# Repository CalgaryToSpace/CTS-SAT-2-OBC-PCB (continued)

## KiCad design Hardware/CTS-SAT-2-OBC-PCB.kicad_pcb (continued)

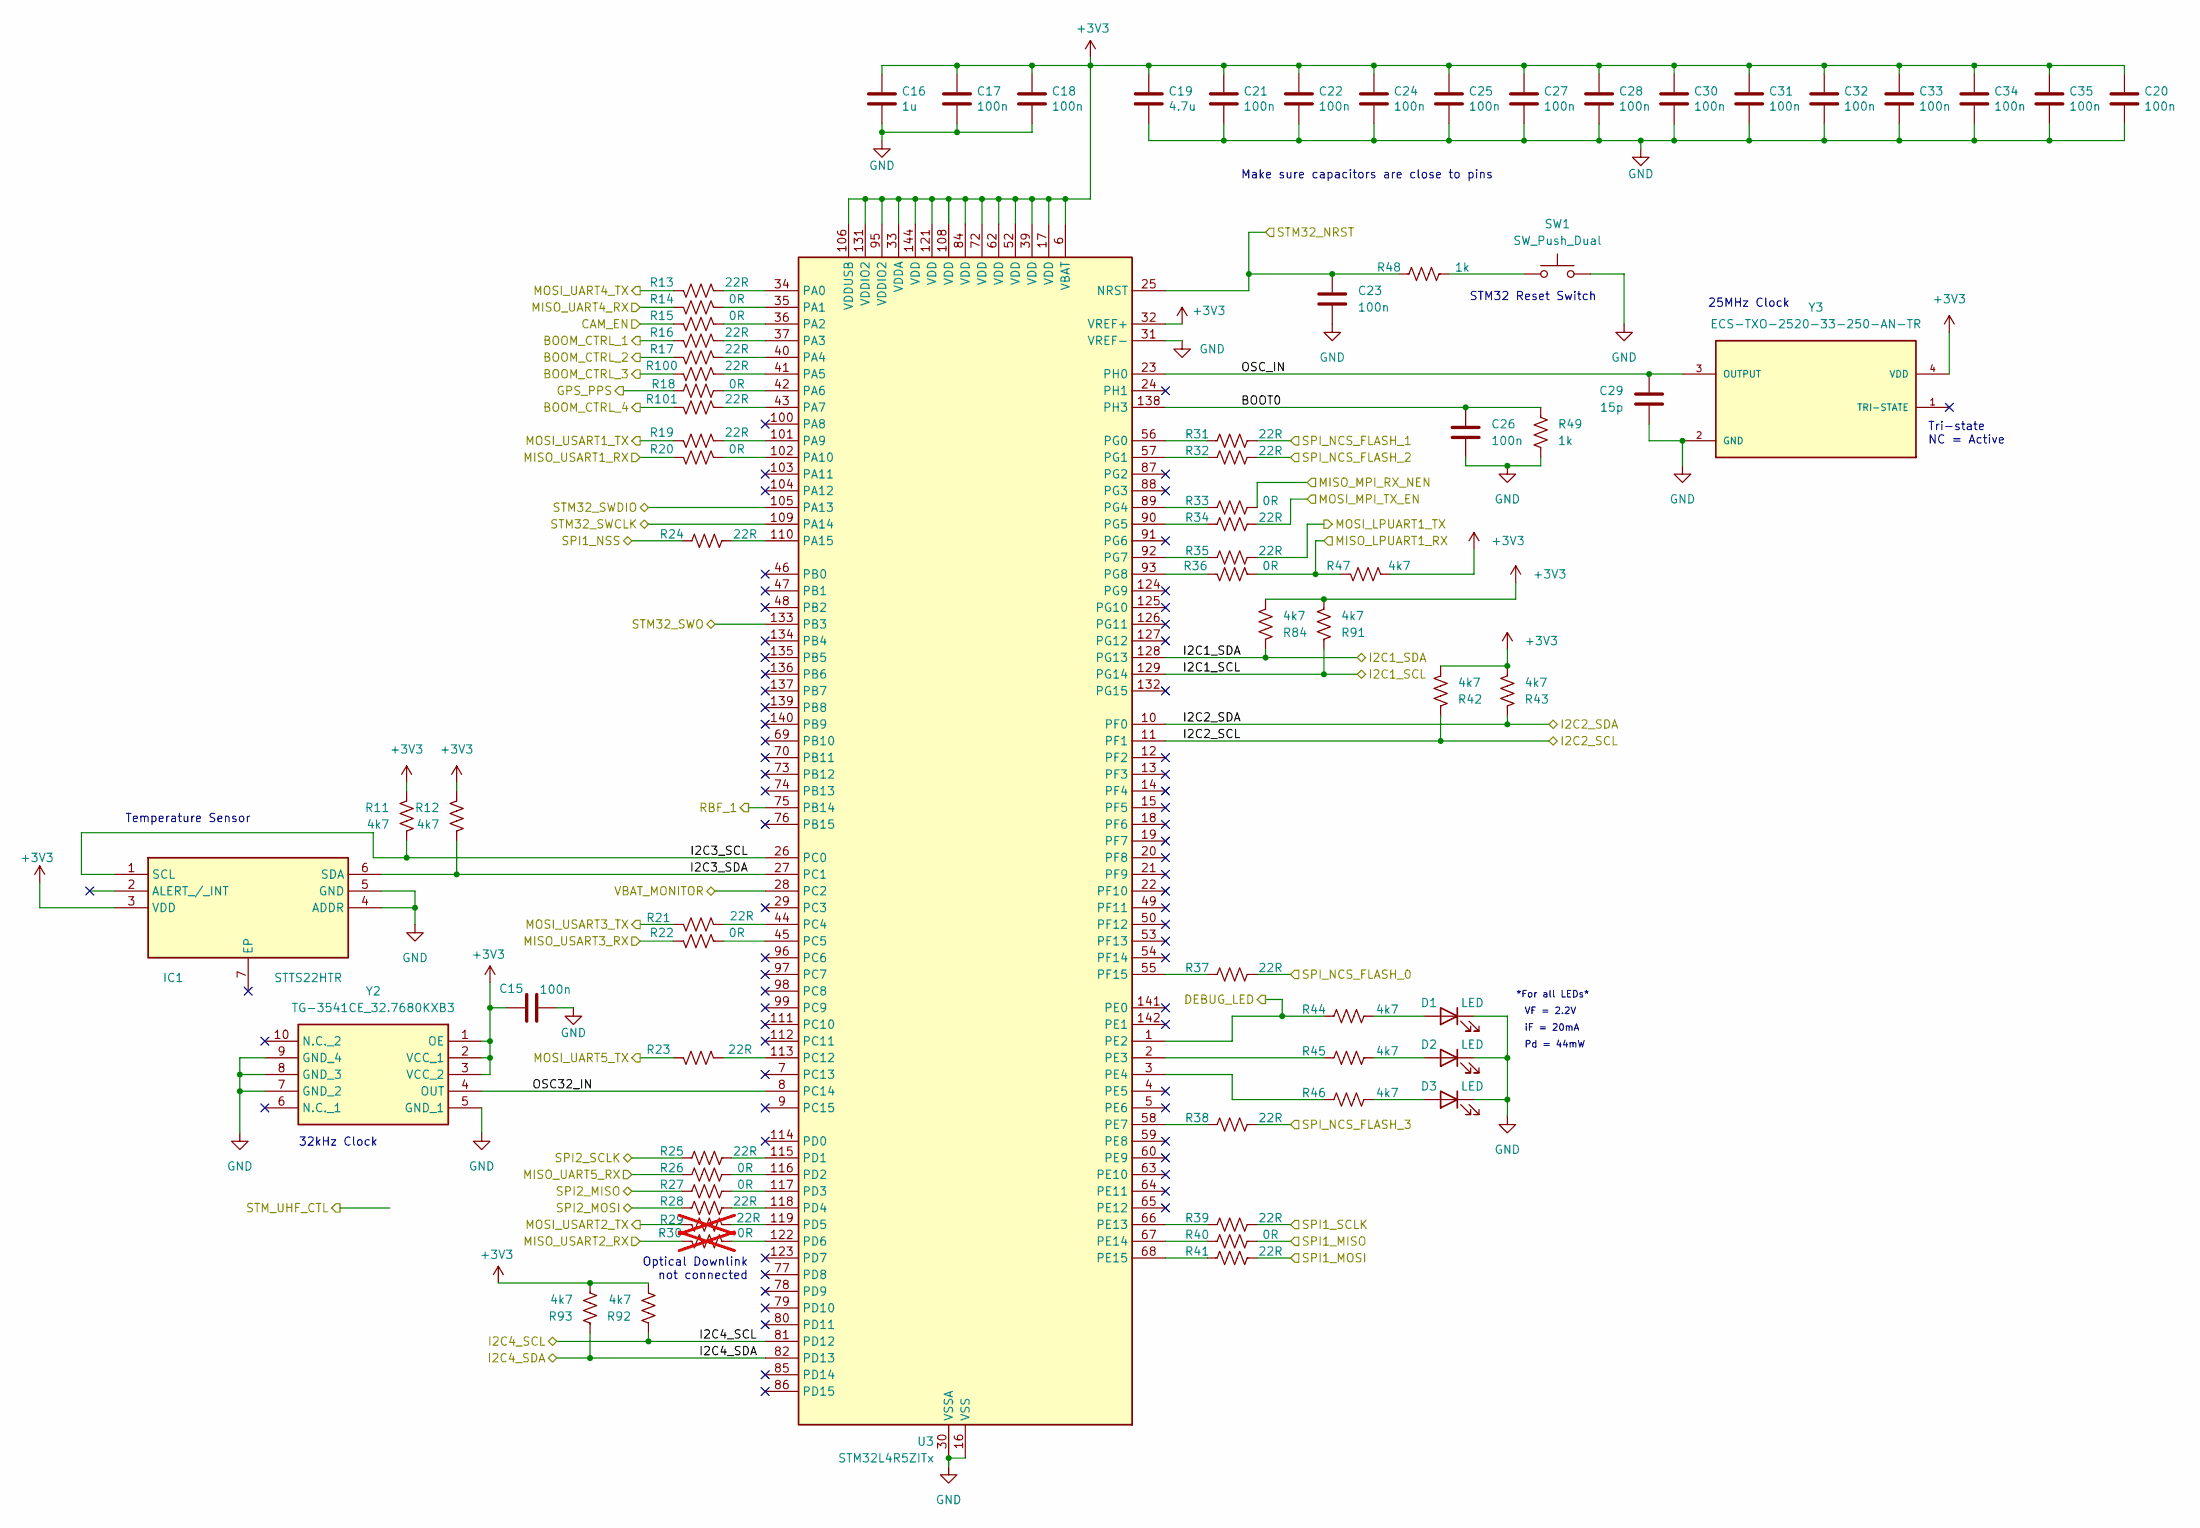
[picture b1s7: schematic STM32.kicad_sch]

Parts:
C15, C17, C18, C20, C21, C22, C24, C25, C27, C28, C30, C31, C32, C33, C34, C35: 100n; C_0402_1005Metric
C16: 1u; C_0402_1005Metric
C19: 4.7u; C_0402_1005Metric
C23, C26: 100n; C_0603_1608Metric
C29: 15p; C_0603_1608Metric
D1, D2, D3: LED; D-SML-D12U1WT86
IC1: STTS22HTR; SON65P200X200X55-7N-D; Manufacturer_Part_Number STTS22HTR; Mouser Part Number 511-STTS22HTR
R11, R12, R42, R43, R44, R45, R46, R47, R84, R91, R92, R93: 4k7; R_0603_1608Metric
R13, R16, R17, R19, R21, R23, R24, R25, R28, R31, R32, R34, R35, R37, R38, R39, R41, R100, R101: 22R; R_0603_1608Metric
R14, R15, R18, R20, R22, R26, R27, R33, R36, R40: 0R; R_0603_1608Metric
R29: 22R; R_0603_1608Metric; not fitted
R30: 0R; R_0603_1608Metric; not fitted
R48, R49: 1k; R_0603_1608Metric
SW1: SW_Push_Dual; SMT_FS
U3: STM32L4R5ZITx; LQFP-144_20x20mm_P0.5mm
Y2: TG-3541CE_32.7680KXB3; TG3541CE327680KXB3; Mouser Part Number 732-TG3541CE32768XB3
Y3: ECS-TXO-2520-33-250-AN-TR; OSC_ECS-TXO-2520-33-250-AN-TR; PARTREV 2017; DigiKey_Part_Number XC2258CT-ND

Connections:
+3V3: C15.1, C16.1, C17.1, C18.1, C19.1, C20.1, C21.1, C22.1, C24.1, C25.1, C27.1, C28.1, C30.1, C31.1, C32.1, C33.1, C34.1, C35.1, IC1.3 (VDD), R11.1, R12.1, R42.2, R43.2, R47.1, R84.2, R91.2, R92.2, R93.2, U3.6 (VBAT), U3.17 (VDD), U3.32 (VREF+), U3.33 (VDDA), U3.39 (VDD), U3.52 (VDD), U3.62 (VDD), U3.72 (VDD), U3.84 (VDD), U3.95 (VDDIO2), U3.106 (VDDUSB), U3.108 (VDD), U3.121 (VDD), U3.131 (VDDIO2), U3.144 (VDD), Y2.1 (OE), Y2.2 (VCC_1), Y2.3 (VCC_2), Y3.4 (VDD); also elsewhere on the board
/Connectors/BOOM_CTRL_1: R16.2; also elsewhere on the board
/Connectors/BOOM_CTRL_2: R17.2; also elsewhere on the board
/Connectors/BOOM_CTRL_3: R100.2; also elsewhere on the board
/Connectors/BOOM_CTRL_4: R101.2; also elsewhere on the board
/Connectors/CAM_EN: R15.2; also elsewhere on the board
/Connectors/DEBUG_LED: R44.1, U3.1 (PE2); also elsewhere on the board
/Connectors/GPS_PPS: R18.1; also elsewhere on the board
/Connectors/MISO_LPUART1_RX: R36.1, R47.2; also elsewhere on the board
/Connectors/MISO_UART4_RX: R14.2; also elsewhere on the board
/Connectors/MISO_UART5_RX: R26.1; also elsewhere on the board
/Connectors/MISO_USART3_RX: R22.2; also elsewhere on the board
/Connectors/MOSI_LPUART1_TX: R35.2; also elsewhere on the board
/Connectors/MOSI_UART4_TX: R13.2; also elsewhere on the board
/Connectors/MOSI_UART5_TX: R23.2; also elsewhere on the board
/Connectors/MOSI_USART3_TX: R21.2; also elsewhere on the board
/Connectors/RBF_1: U3.75 (PB14); also elsewhere on the board
/Connectors/STM32_NRST: C23.1, R48.1, U3.25 (NRST); also elsewhere on the board
/Connectors/STM32_SWCLK: U3.109 (PA14); also elsewhere on the board
/Connectors/STM32_SWDIO: U3.105 (PA13); also elsewhere on the board
/Connectors/STM32_SWO: U3.133 (PB3); also elsewhere on the board
/Connectors/VBAT_MONITOR: U3.28 (PC2); also elsewhere on the board
/MPI/MISO_MPI_RX_NEN: R33.2; also elsewhere on the board
/MPI/MISO_USART1_RX: R20.2; also elsewhere on the board
/MPI/MOSI_MPI_TX_EN: R34.2; also elsewhere on the board
/MPI/MOSI_USART1_TX: R19.2; also elsewhere on the board
/Memory/SPI_FLASH_MISO: R27.1; also elsewhere on the board
/Memory/SPI_FLASH_MOSI: R28.1; also elsewhere on the board
/Memory/SPI_FLASH_SCLK: R25.1; also elsewhere on the board
/Memory/SPI_NCS_FLASH_0: R37.2; also elsewhere on the board
/Memory/SPI_NCS_FLASH_1: R31.2; also elsewhere on the board
/Memory/SPI_NCS_FLASH_2: R32.2; also elsewhere on the board
/Memory/SPI_NCS_FLASH_3: R38.2; also elsewhere on the board
/RP2040/SPI1_CS0: R24.1; also elsewhere on the board
/RP2040/SPI1_RX: R41.2; also elsewhere on the board
/RP2040/SPI1_SCK: R39.2; also elsewhere on the board
/RP2040/SPI1_TX: R40.2; also elsewhere on the board
/STM32/BOOT0: C26.1, R49.1, U3.138 (PH3)
/STM32/I2C1_SCL: R91.1, U3.129 (PG14); also elsewhere on the board
/STM32/I2C1_SDA: R84.1, U3.128 (PG13); also elsewhere on the board
/STM32/I2C2_SCL: R42.1, U3.11 (PF1); also elsewhere on the board
/STM32/I2C2_SDA: R43.1, U3.10 (PF0); also elsewhere on the board
/STM32/I2C3_SCL: IC1.1 (SCL), R11.2, U3.26 (PC0)
/STM32/I2C3_SDA: IC1.6 (SDA), R12.2, U3.27 (PC1)
/STM32/I2C4_SCL: R92.1, U3.81 (PD12); also elsewhere on the board
/STM32/I2C4_SDA: R93.1, U3.82 (PD13); also elsewhere on the board
/STM32/OSC32_IN: U3.8 (PC14), Y2.4 (OUT)
/STM32/OSC_IN: C29.1, U3.23 (PH0), Y3.3 (OUTPUT)
GND: C15.2, C16.2, C17.2, C18.2, C19.2, C20.2, C21.2, C22.2, C23.2, C24.2, C25.2, C26.2, C27.2, C28.2, C29.2, C30.2, C31.2, C32.2, C33.2, C34.2, C35.2, D1.1 (K), D2.1 (K), D3.1 (K), IC1.4 (ADDR), IC1.5 (GND), R49.2, SW1.2, U3.16 (VSS), U3.30 (VSSA), U3.31 (VREF-), U3.38 (VSS), U3.51 (VSS), U3.61 (VSS), U3.71 (VSS), U3.83 (VSS), U3.94 (VSS), U3.107 (VSS), U3.120 (VSS), U3.130 (VSS), U3.143 (VSS), Y2.5 (GND_1), Y2.7 (GND_2), Y2.8 (GND_3), Y2.9 (GND_4), Y3.2 (GND); also elsewhere on the board
unnamed: D1.2 (A), R44.2
unnamed: D2.2 (A), R45.2
unnamed: D3.2 (A), R46.2
unnamed: R48.2, SW1.1
unnamed: R13.1, U3.34 (PA0)
unnamed: R14.1, U3.35 (PA1)
unnamed: R15.1, U3.36 (PA2)
unnamed: R16.1, U3.37 (PA3)
unnamed: R17.1, U3.40 (PA4)
unnamed: R100.1, U3.41 (PA5)
unnamed: R18.2, U3.42 (PA6)
unnamed: R101.1, U3.43 (PA7)
unnamed: R19.1, U3.101 (PA9)
unnamed: R20.1, U3.102 (PA10)
unnamed: R24.2, U3.110 (PA15)
unnamed: R21.1, U3.44 (PC4)
unnamed 168: R22.1, U3.45 (PC5); also elsewhere on the board
unnamed: R23.1, U3.113 (PC12)
unnamed: R25.2, U3.115 (PD1)
unnamed: R26.2, U3.116 (PD2)
unnamed: R27.2, U3.117 (PD3)
unnamed: R28.2, U3.118 (PD4)
unnamed: R29.1, U3.119 (PD5)
unnamed: R30.1, U3.122 (PD6)
unnamed: R45.1, U3.2 (PE3)
unnamed: R46.1, U3.3 (PE4)
unnamed: R38.1, U3.58 (PE7)
unnamed: R39.1, U3.66 (PE13)
unnamed: R40.1, U3.67 (PE14)
unnamed: R41.1, U3.68 (PE15)
unnamed: R37.1, U3.55 (PF15)
unnamed: R31.1, U3.56 (PG0)
unnamed: R32.1, U3.57 (PG1)
unnamed: R33.1, U3.89 (PG4)
unnamed: R34.1, U3.90 (PG5)
unnamed: R35.1, U3.92 (PG7)
unnamed: R36.2, U3.93 (PG8)

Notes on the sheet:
Optical Downlink not connected
32kHz Clock
25MHz Clock
VF = 2.2V
STM32 Reset Switch
Tri-state NC = Active
Make sure capacitors are close to pins
Pd = 44mW
*For all LEDs*
Temperature Sensor
iF = 20mA

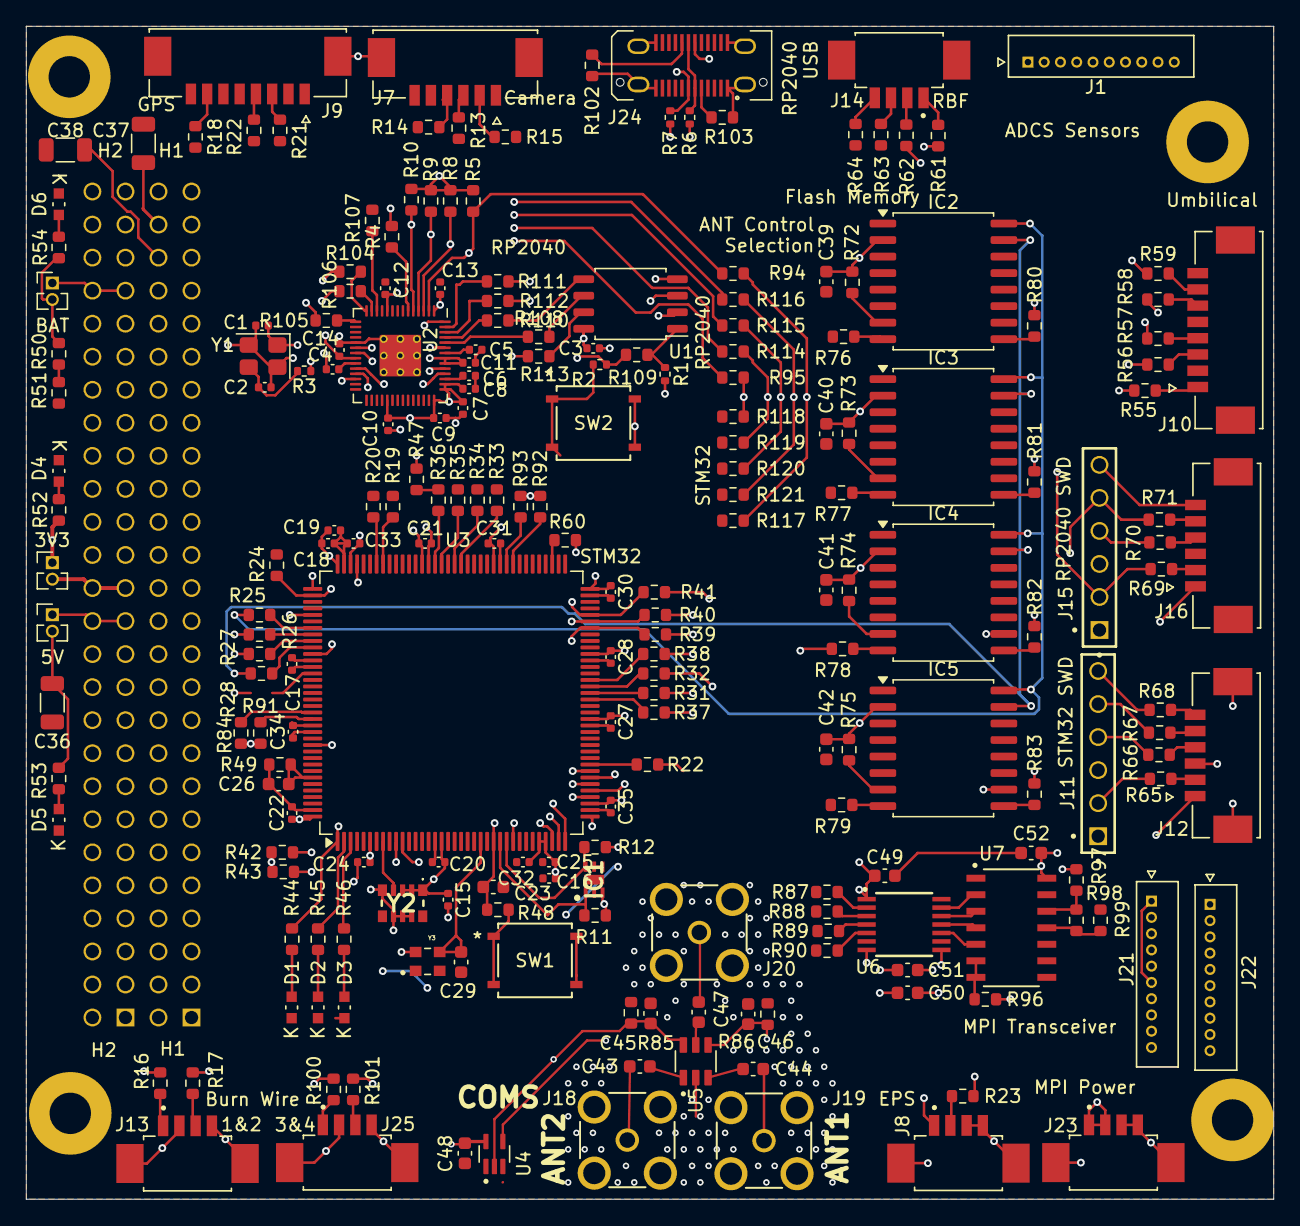
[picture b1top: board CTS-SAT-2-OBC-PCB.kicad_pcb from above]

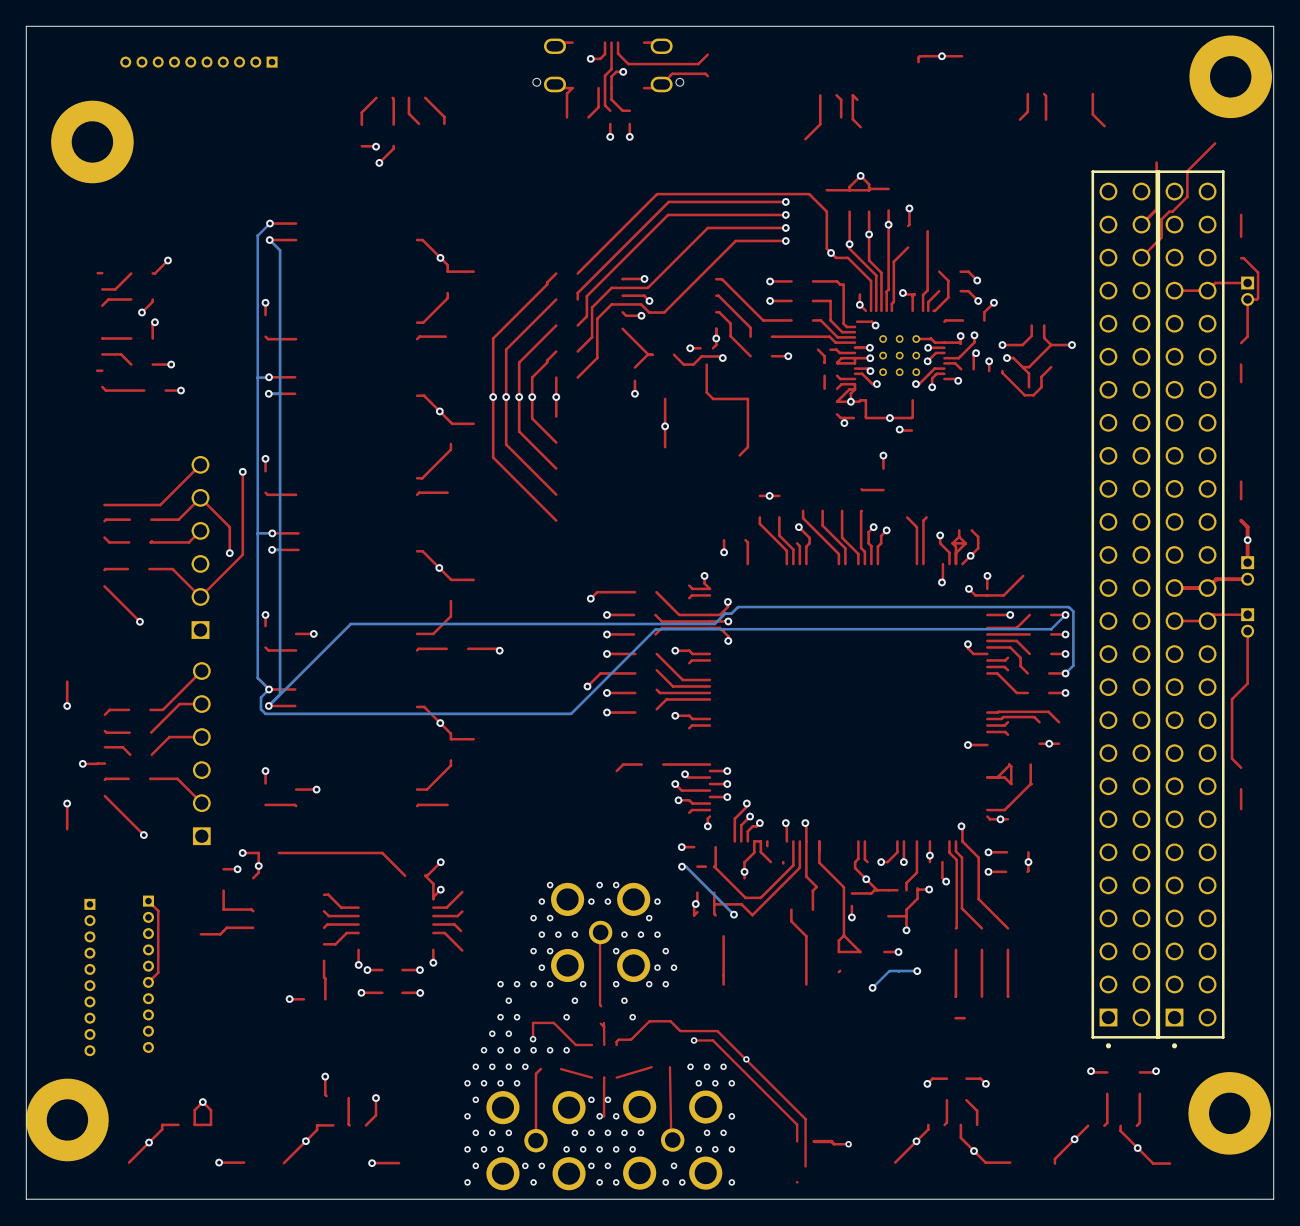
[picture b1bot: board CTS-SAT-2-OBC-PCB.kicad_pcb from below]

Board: 6 copper layers, 95.9 x 90.2 mm, 223 parts (2 on the bottom side), 182 nets.

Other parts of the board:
*1, *2, *3, *4: PC104 Mounting; PC104 MOUNTING POINTS
R22#2: 0R; R_0603_1608Metric

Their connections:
/Connectors/MISO_USART3_RX: R22#2.2; also elsewhere on the board
unnamed 168: R22#2.1; also elsewhere on the board

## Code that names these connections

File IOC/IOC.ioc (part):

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Mcu.Name=STM32L4R5Z(G-I)Tx
Mcu.Package=LQFP144
Mcu.UserName=STM32L4R5ZITx
PA0.GPIOParameters=GPIO_Label
PA0.GPIO_Label=PIN_CAMERA_MOSI_UART4_TX
PA0.Mode=Asynchronous
PA0.Signal=UART4_TX
PA1.GPIOParameters=GPIO_Label
PA1.GPIO_Label=PIN_CAMERA_MISO_UART4_RX
PA1.Mode=Asynchronous
PA1.Signal=UART4_RX
PA10.GPIOParameters=GPIO_Label
PA10.GPIO_Label=PIN_MPI_MISO_USART1_RX
PA10.Mode=Asynchronous
PA10.Signal=USART1_RX
PA13\ (JTMS/SWDIO).GPIOParameters=GPIO_Label
PA13\ (JTMS/SWDIO).GPIO_Label=PIN_SWDIO
PA13\ (JTMS/SWDIO).Mode=Serial_Wire
PA13\ (JTMS/SWDIO).Signal=SYS_JTMS-SWDIO
PA14\ (JTCK/SWCLK).GPIOParameters=GPIO_Label
PA14\ (JTCK/SWCLK).GPIO_Label=PIN_SWCLK
PA14\ (JTCK/SWCLK).Mode=Serial_Wire
PA14\ (JTCK/SWCLK).Signal=SYS_JTCK-SWCLK
PA15\ (JTDI).GPIOParameters=GPIO_Label
PA15\ (JTDI).GPIO_Label=PIN_RP2040_SPI1_NSS
PA15\ (JTDI).Signal=SPI1_NSS
PA2.Signal=ADCx_IN7
PA3.Signal=ADCx_IN8
PA4.Signal=ADCx_IN9
PA5.Signal=ADCx_IN10
PA6.Signal=ADCx_IN11
PA7.Signal=ADCx_IN12
PA9.GPIOParameters=GPIO_Label
PA9.GPIO_Label=PIN_MPI_MOSI_USART1_TX
PA9.Mode=Asynchronous
PA9.Signal=USART1_TX
PB0.Signal=ADCx_IN15
PB1.Signal=ADCx_IN16
PB12.GPIOParameters=GPIO_Label
PB12.GPIO_Label=PIN_UHF_CTRL_OUT
PB12.Signal=GPIO_Output
PB14.GPIOParameters=GPIO_Label
PB14.GPIO_Label=PIN_REMOVE_BEFORE_FLIGHT_LOW_IS_FLYING_IN
PB14.Signal=GPIO_Input
PB2.GPIOParameters=GPIO_Label
PB2.GPIO_Label=PIN_BOOM_DEPLOY_EN_1_OUT
PB2.Signal=GPIO_Output
PB3\ (JTDO/TRACESWO).GPIOParameters=GPIO_Label
PB3\ (JTDO/TRACESWO).GPIO_Label=PIN_SWO
PB3\ (JTDO/TRACESWO).Signal=SYS_JTDO-SWO
PB7.GPIOParameters=GPIO_Label
PB7.GPIO_Label=PIN_LED_DEVKIT_LD2
PB7.Signal=GPIO_Output
PC0.GPIOParameters=GPIO_Label
PC0.GPIO_Label=PIN_ANTENNA_B_I2C3_SCL
PC0.Mode=I2C
PC0.Signal=I2C3_SCL
PC1.GPIOParameters=GPIO_Label
PC1.GPIO_Label=PIN_ANTENNA_B_I2C3_SDA
PC1.Mode=I2C
PC1.Signal=I2C3_SDA
PC12.GPIOParameters=GPIO_Label
PC12.GPIO_Label=PIN_EPS_MOSI_UART_TX
PC12.Mode=Asynchronous
PC12.Signal=UART5_TX
PC14-OSC32_IN\ (PC14).GPIOParameters=GPIO_Label
PC14-OSC32_IN\ (PC14).GPIO_Label=PIN_PC14_OSC32_IN
PC14-OSC32_IN\ (PC14).Signal=RCC_OSC32_IN
PC2.GPIOParameters=GPIO_Label
PC2.GPIO_Label=PIN_ADC_READ_VBAT_VOLTAGE
PC2.Signal=ADCx_IN3
PC3.Signal=ADCx_IN4
PC4.GPIOParameters=GPIO_Label
PC4.GPIO_Label=PIN_GNSS_MOSI_USART3_TX
PC4.Mode=Asynchronous
PC4.Signal=USART3_TX
PC5.GPIOParameters=GPIO_Label
PC5.GPIO_Label=PIN_GNSS_MISO_USART3_RX
PC5.Mode=Asynchronous
PC5.Signal=USART3_RX
PD1.GPIOParameters=GPIO_Label
PD1.GPIO_Label=PIN_MEM_SPI2_SCK
PD1.Signal=SPI2_SCK
PD12.GPIOParameters=GPIO_Label
PD12.GPIO_Label=PIN_TEMP_SENSOR_I2C4_SCL
PD12.Mode=I2C
PD12.Signal=I2C4_SCL
PD13.GPIOParameters=GPIO_Label
PD13.GPIO_Label=PIN_TEMP_SENSOR_I2C4_SDA
PD13.Mode=I2C
PD13.Signal=I2C4_SDA
PD2.GPIOParameters=GPIO_Label
PD2.GPIO_Label=PIN_EPS_MISO_UART_RX
PD2.Mode=Asynchronous
PD2.Signal=UART5_RX
PD3.GPIOParameters=GPIO_Label
PD3.GPIO_Label=PIN_MEM_SPI2_MISO
PD3.Signal=SPI2_MISO
PD4.GPIOParameters=GPIO_Label
PD4.GPIO_Label=PIN_MEM_SPI2_MOSI
PD4.Signal=SPI2_MOSI
PD5.GPIOParameters=GPIO_Label
PD5.GPIO_Label=PIN_AX100_MISO_USART2_RX
PD5.Mode=Asynchronous
PD5.Signal=USART2_TX
PD6.GPIOParameters=GPIO_Label
PD6.GPIO_Label=PIN_AX100_MOSI_USART2_TX
PD6.Mode=Asynchronous
PD6.Signal=USART2_RX
PE10.Signal=GPIO_Output
PE13.GPIOParameters=GPIO_Label
PE13.GPIO_Label=PIN_RP2040_SPI1_SCLK
PE13.Mode=Full_Duplex_Master
PE13.Signal=SPI1_SCK
PE14.GPIOParameters=GPIO_Label
PE14.GPIO_Label=PIN_RP2040_SPI1_MISO
PE14.Mode=Full_Duplex_Master
PE14.Signal=SPI1_MISO
PE15.GPIOParameters=GPIO_Label
PE15.GPIO_Label=PIN_RP2040_SPI1_MOSI
PE15.Mode=Full_Duplex_Master
PE15.Signal=SPI1_MOSI
PE2.GPIOParameters=GPIO_Label
PE2.GPIO_Label=PIN_LED_GP1_OUT
PE2.Signal=GPIO_Output
PE3.GPIOParameters=GPIO_Label
PE3.GPIO_Label=PIN_LED_GP2_OUT
PE3.Signal=GPIO_Output
PE4.GPIOParameters=GPIO_Label
PE4.GPIO_Label=PIN_LED_GP3_OUT
PE4.Signal=GPIO_Output
PE7.GPIOParameters=GPIO_Label
PE7.GPIO_Label=PIN_MEM_NCS_FLASH_0
PE7.Signal=GPIO_Output
PE8.GPIOParameters=GPIO_Label
PE8.GPIO_Label=PIN_MEM_NCS_FRAM_1
PE8.Signal=GPIO_Output
PE9.GPIOParameters=GPIO_Label
PE9.GPIO_Label=PIN_MEM_NCS_FRAM_0
PE9.Signal=GPIO_Output
PF0.GPIOParameters=GPIO_Label
PF0.GPIO_Label=PIN_ANTENNA_A_I2C2_SDA
PF0.Mode=I2C
PF0.Signal=I2C2_SDA
PF1.GPIOParameters=GPIO_Label
PF1.GPIO_Label=PIN_ANTENNA_A_I2C2_SCL
PF1.Mode=I2C
PF1.Signal=I2C2_SCL
PF10.GPIOParameters=GPIO_Label
PF10.GPIO_Label=PIN_CAM_EN_OUT
PF10.Signal=GPIO_Output
PF11.GPIOParameters=GPIO_Label
PF11.GPIO_Label=PIN_BOOM_DEPLOY_EN_2_OUT
PF11.Signal=GPIO_Output
PF12.GPIOParameters=GPIO_Label
PF12.GPIO_Label=PIN_BOOM_DEPLOY_EN_3_OUT
PF12.Signal=GPIO_Output
PF13.GPIOParameters=GPIO_Label
PF13.GPIO_Label=PIN_GNSS_PPS_IN
PF13.Signal=GPXTI13
PF14.GPIOParameters=GPIO_Label
PF14.GPIO_Label=PIN_BOOM_DEPLOY_EN_4_OUT
PF14.Signal=GPIO_Output
PF15.GPIOParameters=GPIO_Label
PF15.GPIO_Label=PIN_MEM_NCS_FLASH_3
PF15.Signal=GPIO_Output
PG0.GPIOParameters=GPIO_Label
PG0.GPIO_Label=PIN_MEM_NCS_FLASH_2
PG0.Signal=GPIO_Output
PG1.GPIOParameters=GPIO_Label
PG1.GPIO_Label=PIN_MEM_NCS_FLASH_1
PG1.Signal=GPIO_Output
PG13.GPIOParameters=GPIO_Label
PG13.GPIO_Label=PIN_STACK_I2C1_SDA
PG13.Mode=I2C
PG13.Signal=I2C1_SDA
PG14.GPIOParameters=GPIO_Label
PG14.GPIO_Label=PIN_STACK_I2C1_SCL
PG14.Mode=I2C
PG14.Signal=I2C1_SCL
PG4.GPIOParameters=GPIO_Label
PG4.GPIO_Label=PIN_MPI_NEN_RX_MISO_OUT
PG4.Signal=GPIO_Output
PG5.GPIOParameters=GPIO_Label
PG5.GPIO_Label=PIN_MPI_EN_TX_MOSI_OUT
PG5.Signal=GPIO_Output
PG7.GPIOParameters=GPIO_Label
PG7.GPIO_Label=PIN_DEBUG_MOSI_LPUART1_TX
PG7.Mode=Asynchronous
PG7.Signal=LPUART1_TX
PG8.GPIOParameters=GPIO_Label
PG8.GPIO_Label=PIN_DEBUG_MISO_LPUART1_RX
PG8.Mode=Asynchronous
PG8.Signal=LPUART1_RX
PH0-OSC_IN\ (PH0).GPIOParameters=GPIO_Label
PH0-OSC_IN\ (PH0).GPIO_Label=PIN_PH0_OSC_IN
PH0-OSC_IN\ (PH0).Mode=HSE-External-Oscillator
PH0-OSC_IN\ (PH0).Signal=RCC_OSC_IN
PH1-OSC_OUT\ (PH1).Mode=HSE-External-Oscillator
PH1-OSC_OUT\ (PH1).Signal=RCC_OSC_OUT
PH3-BOOT0.GPIOParameters=GPIO_Label
PH3-BOOT0.GPIO_Label=PIN_BOOT0
PH3-BOOT0.Signal=GPIO_Input
RCC.HSE_VALUE=8000000
RCC.SYSCLKFreq_VALUE=16000000
RCC.SYSCLKSource=RCC_SYSCLKSOURCE_HSI
board=custom

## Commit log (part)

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2026-01-10 Create KiCad project
2026-01-10 Add processor symbols to schematic
2026-01-10 Connect RP2040, STM32, temperature sensor
2026-01-14 Add PC104 header sub-schematic
2026-01-17 Add STM32 I2C and SPI connections
2026-01-17 Add UARTs to STM32
2026-01-17 Add remaining STM32 connections
2026-01-17 Assign SPI1 to Pi 4 <--> STM32
2026-01-21 Small updates
2026-01-21 Fix RP2040 1V1
2026-01-24 RP2040 Schematic
2026-01-24 Add fast clock
2026-01-24 minor fix
2026-01-29 STM32 Flash Memory
2026-01-30 STM32 RTC
2026-01-30 prepare for FRAM
2026-01-31 Begin with connectors
2026-02-04 Import CTS-SAT-1 PCB
2026-02-04 Remove extraneous objects
    Removed: FRAM, PC104 pull-downs, Altium data
2026-02-04 Begin importing to SAT-2 PCB
2026-02-07 Connect connectors
2026-02-07 Add STM32 Reset Switch & RP2040 I2C pins
2026-02-07 Move ANT to RP2040
2026-02-07 Add RP2040 SWD
2026-02-13 Finish schematic v1
2026-02-13 Fix RP2040 BOOTSEL
2026-02-17 Add IOC and second burnwire connector
2026-02-21 Prepare for layout
2026-02-28 Assign footprints
2026-02-28 Update USB connector to USBC
2026-02-28 Add USBC pull-downs
2026-03-07 Basic board shape
2026-03-07 Fix diode footprint assignments
2026-03-07 Place connectors
2026-03-11 Resistors for connectors
2026-03-14 make most changes from design review
2026-03-14 H1/2 capacitors and LEDs
2026-03-14 STM32 capacitors
2026-04-08 Place RP2040
2026-04-08 RP2040 Peripherals
2026-04-08 minor labels
2026-04-11 Memory
2026-04-11 MPI layout
2026-04-11 Comms
2026-04-11 STM32
2026-04-11 Layout Revision 1
2026-04-11 Refill zones
2026-04-11 Add NC pins
2026-05-23 3V3 plane
2026-05-23 Begin routing
2026-05-23 Continue routing
2026-06-06 Replace Optical Downlink with ADCS Sensors connector
2026-06-06 Update schematic to allow using STM32 alone
2026-06-06 Adjust Comms layout
2026-06-06 minor routing change for comms
2026-06-13 Populate more resistors
2026-06-13 3V3 routing
2026-06-20 Reroute power
2026-06-20 special 3V3 lines
2026-06-20 H1, H2 routing
2026-06-20 more routing
2026-06-20 route most connectors
